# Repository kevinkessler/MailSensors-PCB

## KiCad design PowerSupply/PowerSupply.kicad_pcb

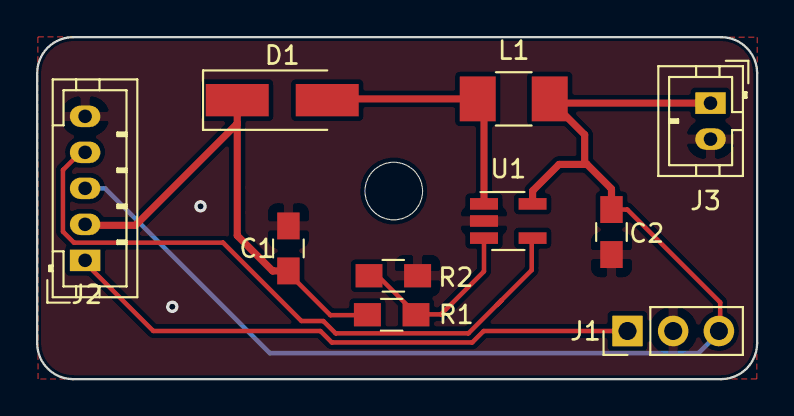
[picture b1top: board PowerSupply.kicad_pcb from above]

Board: 2 copper layers, 40.0 x 19.0 mm, 11 parts (0 on the bottom side), 7 nets.

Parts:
C1: 22uF; C_0805_HandSoldering
C2: 10uF; C_0805_HandSoldering
D1: D_Schottky; D_SMA_Handsoldering
J1: Conn_01x03_Male; Pin_Header_Straight_1x03_Pitch2.54mm
J2: Conn_01x05_Male; JST_PH_B5B-PH-K_05x2.00mm_Straight
J3: Conn_01x02_Male; JST_PH_B2B-PH-K_02x2.00mm_Straight
L1: 10 uH; L_1210_HandSoldering
MP1: MOUNTHOLE; MountingHole_3.2mm_M3
R1: 5.6K; R_0805_HandSoldering
R2: 1.8K; R_0805_HandSoldering
U1: MIC2288; SOT-23-5_HandSoldering

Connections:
+3V3: J1.1, J2.1
+5V: C1.1, D1.1, J2.2, R1.1
+BATT: C2.1, J1.3, J2.3, J3.1, L1.2, U1.5
GND: C1.2, C2.2, J1.2, J2.5, J3.2, R2.2, U1.2
unnamed: D1.2, L1.1, U1.1
unnamed: R1.2, R2.1, U1.3
V5_ENABLE: J2.4, U1.4

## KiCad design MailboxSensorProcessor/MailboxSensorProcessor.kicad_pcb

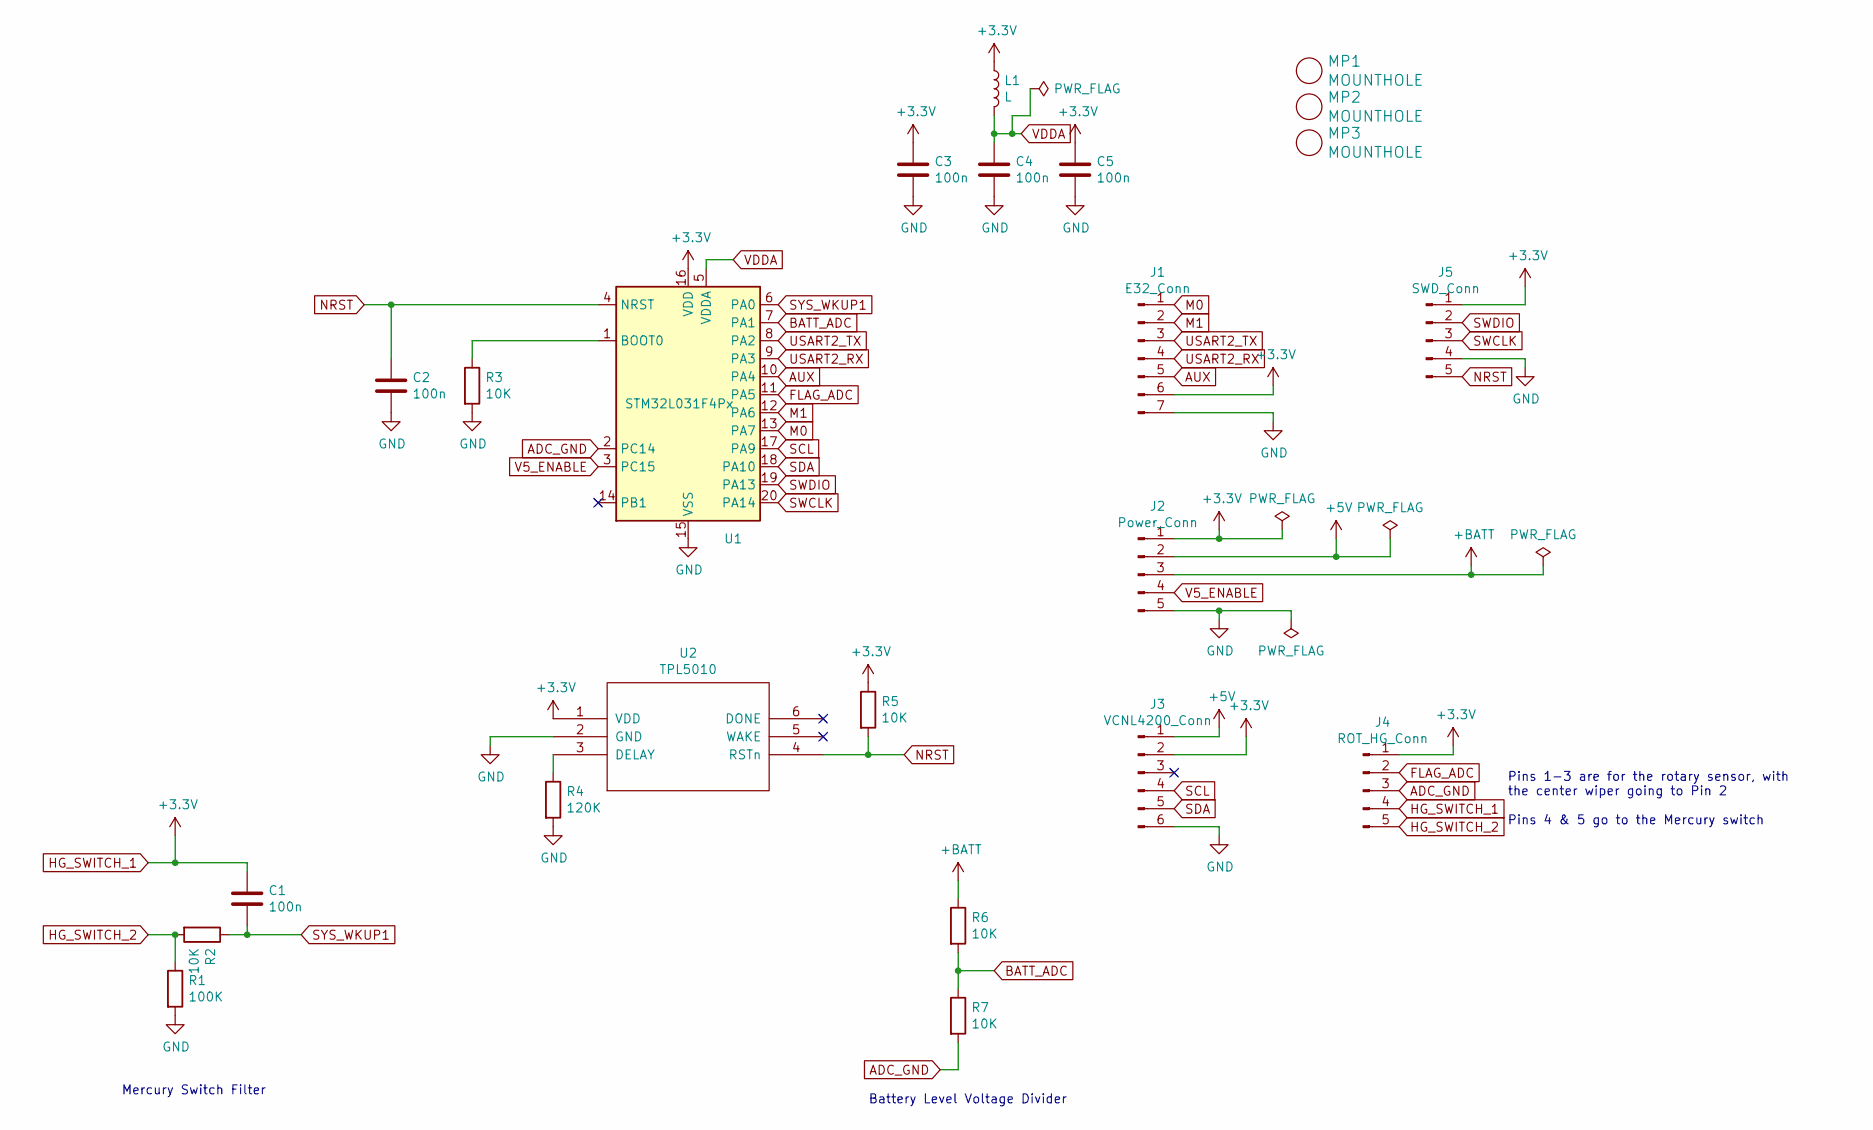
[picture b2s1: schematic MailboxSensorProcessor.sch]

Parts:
C1, C2, C3, C4, C5: 100n; C_0805_HandSoldering
J1: E32_Conn; Pin_Header_Straight_1x07_Pitch2.54mm
J2: Power_Conn; JST_PH_B5B-PH-K_05x2.00mm_Straight
J3: VCNL4200_Conn; JST_PH_B6B-PH-K_06x2.00mm_Straight
J4: ROT_HG_Conn; JST_PH_B5B-PH-K_05x2.00mm_Straight
J5: SWD_Conn; Pin_Header_Straight_1x05_Pitch2.54mm
L1: L; L_0805_HandSoldering
MP1, MP2, MP3: MOUNTHOLE; MountingHole_3.2mm_M3
R1: 100K; R_0805_HandSoldering
R2, R3, R5, R6, R7: 10K; R_0805_HandSoldering
R4: 120K; R_0805_HandSoldering
U1: STM32L031F4Px; TSSOP-20_4.4x6.5mm_Pitch0.65mm
U2: TPL5010; TSOT-23-5_HandSoldering

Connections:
+5V: J2.2, J3.1
+BATT: J2.3, R6.1
ADC_GND: J4.3, R7.2, U1.2 (PC14)
AUX: J1.5, U1.10 (PA4)
BATT_ADC: R6.2, R7.1, U1.7 (PA1)
FLAG_ADC: J4.2, U1.11 (PA5)
GND: C2.2, C3.2, C4.2, C5.2, J1.7, J2.5, J3.6, J5.4, R1.2, R3.2, R4.2, U1.15 (VSS), U2.2 (GND)
HG_SWITCH_1: C1.1, C3.1, C5.1, J1.6, J2.1, J3.2, J4.1, J4.4, J5.1, L1.1, R5.1, U1.16 (VDD), U2.1 (VDD)
HG_SWITCH_2: J4.5, R1.1, R2.2
M0: J1.1, U1.13 (PA7)
M1: J1.2, U1.12 (PA6)
NRST: C2.1, J5.5, R5.2, U1.4 (NRST), U2.4 (RSTn)
unnamed: R3.1, U1.1 (BOOT0)
unnamed: R4.1, U2.3 (DELAY)
SCL: J3.4, U1.17 (PA9)
SDA: J3.5, U1.18 (PA10)
SWCLK: J5.3, U1.20 (PA14)
SWDIO: J5.2, U1.19 (PA13)
SYS_WKUP1: C1.2, R2.1, U1.6 (PA0)
USART2_RX: J1.4, U1.9 (PA3)
USART2_TX: J1.3, U1.8 (PA2)
V5_ENABLE: J2.4, U1.3 (PC15)
VDDA: C4.1, L1.2, U1.5 (VDDA)

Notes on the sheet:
Pins 1-3 are for the rotary sensor, with the center wiper going to Pin 2 Pins 4 & 5 go to the Mercury switch
Battery Level Voltage Divider
Mercury Switch Filter

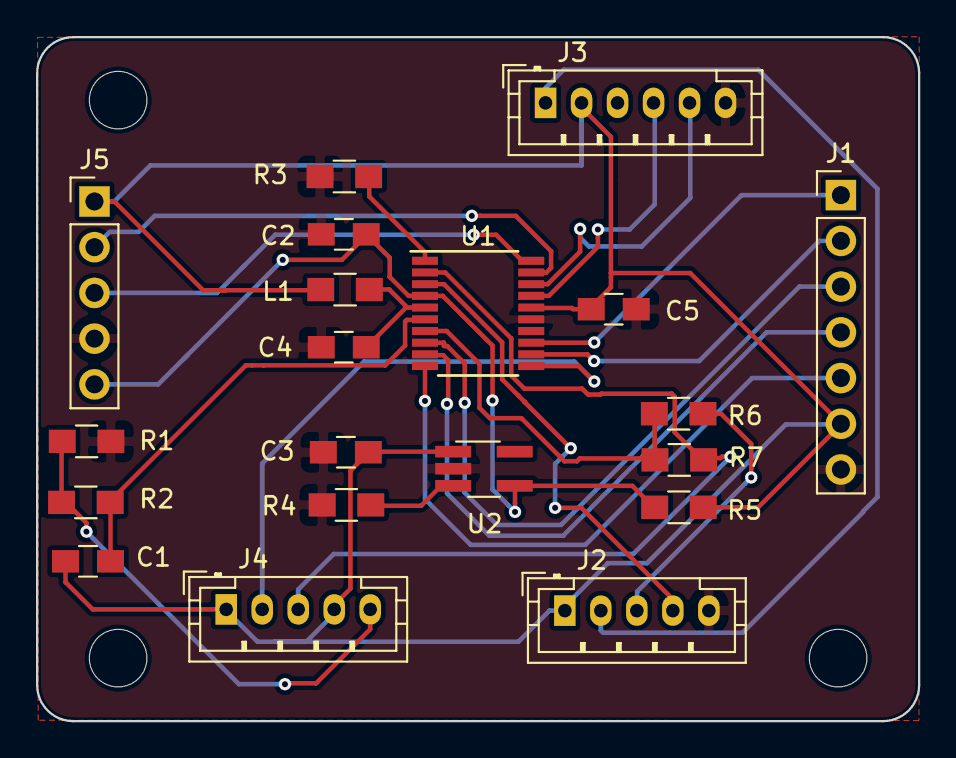
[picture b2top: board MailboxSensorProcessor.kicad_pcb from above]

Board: 2 copper layers, 49.0 x 38.0 mm, 23 parts (0 on the bottom side), 23 nets.

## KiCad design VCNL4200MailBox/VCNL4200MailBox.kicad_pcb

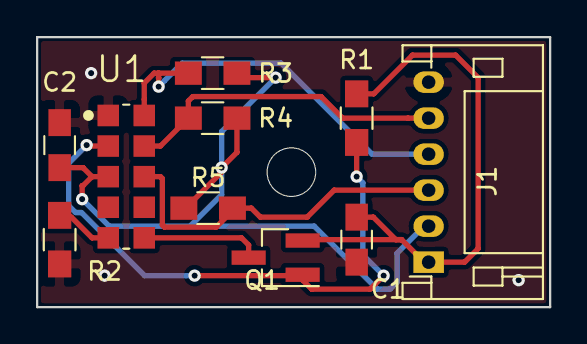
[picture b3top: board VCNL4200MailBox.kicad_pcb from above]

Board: 2 copper layers, 28.5 x 15.0 mm, 11 parts (0 on the bottom side), 9 nets.

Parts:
C1: 2.2u; C_0805_HandSoldering
C2: 100n; C_0805_HandSoldering
J1: Conn_01x06; JST_PH_S6B-PH-K_06x2.00mm_Angled
MP1: MOUNTHOLE; MountingHole_2.7mm_M2.5_ISO7380
Q1: IRLML2244; SOT-23_Handsoldering
R1: 1K; R_0805_HandSoldering
R2: 2.7; R_0805_HandSoldering
R3, R4: 2.2K; R_0805_HandSoldering
R5: 8.2K; R_0805_HandSoldering
U1: VCNL4200; SENSOR_VCNL4200

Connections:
+3V3: C2.1, J1.2, R3.1, R4.1, R5.1, U1.3
+5V: C1.1, J1.1, Q1.2, R1.1
/INT: J1.3, R5.2, U1.8
/SCL: J1.4, R3.2, U1.10
/SDA: J1.5, R4.2, U1.9
GND: C1.2, C2.2, J1.6, R2.2, U1.1
unnamed: Q1.1, R1.2, U1.2
unnamed: Q1.3, U1.6
unnamed: R2.1, U1.5

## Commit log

2019-07-24 README
2019-08-09 Mailbox Sensor PCB
2019-08-09 Power PCB
